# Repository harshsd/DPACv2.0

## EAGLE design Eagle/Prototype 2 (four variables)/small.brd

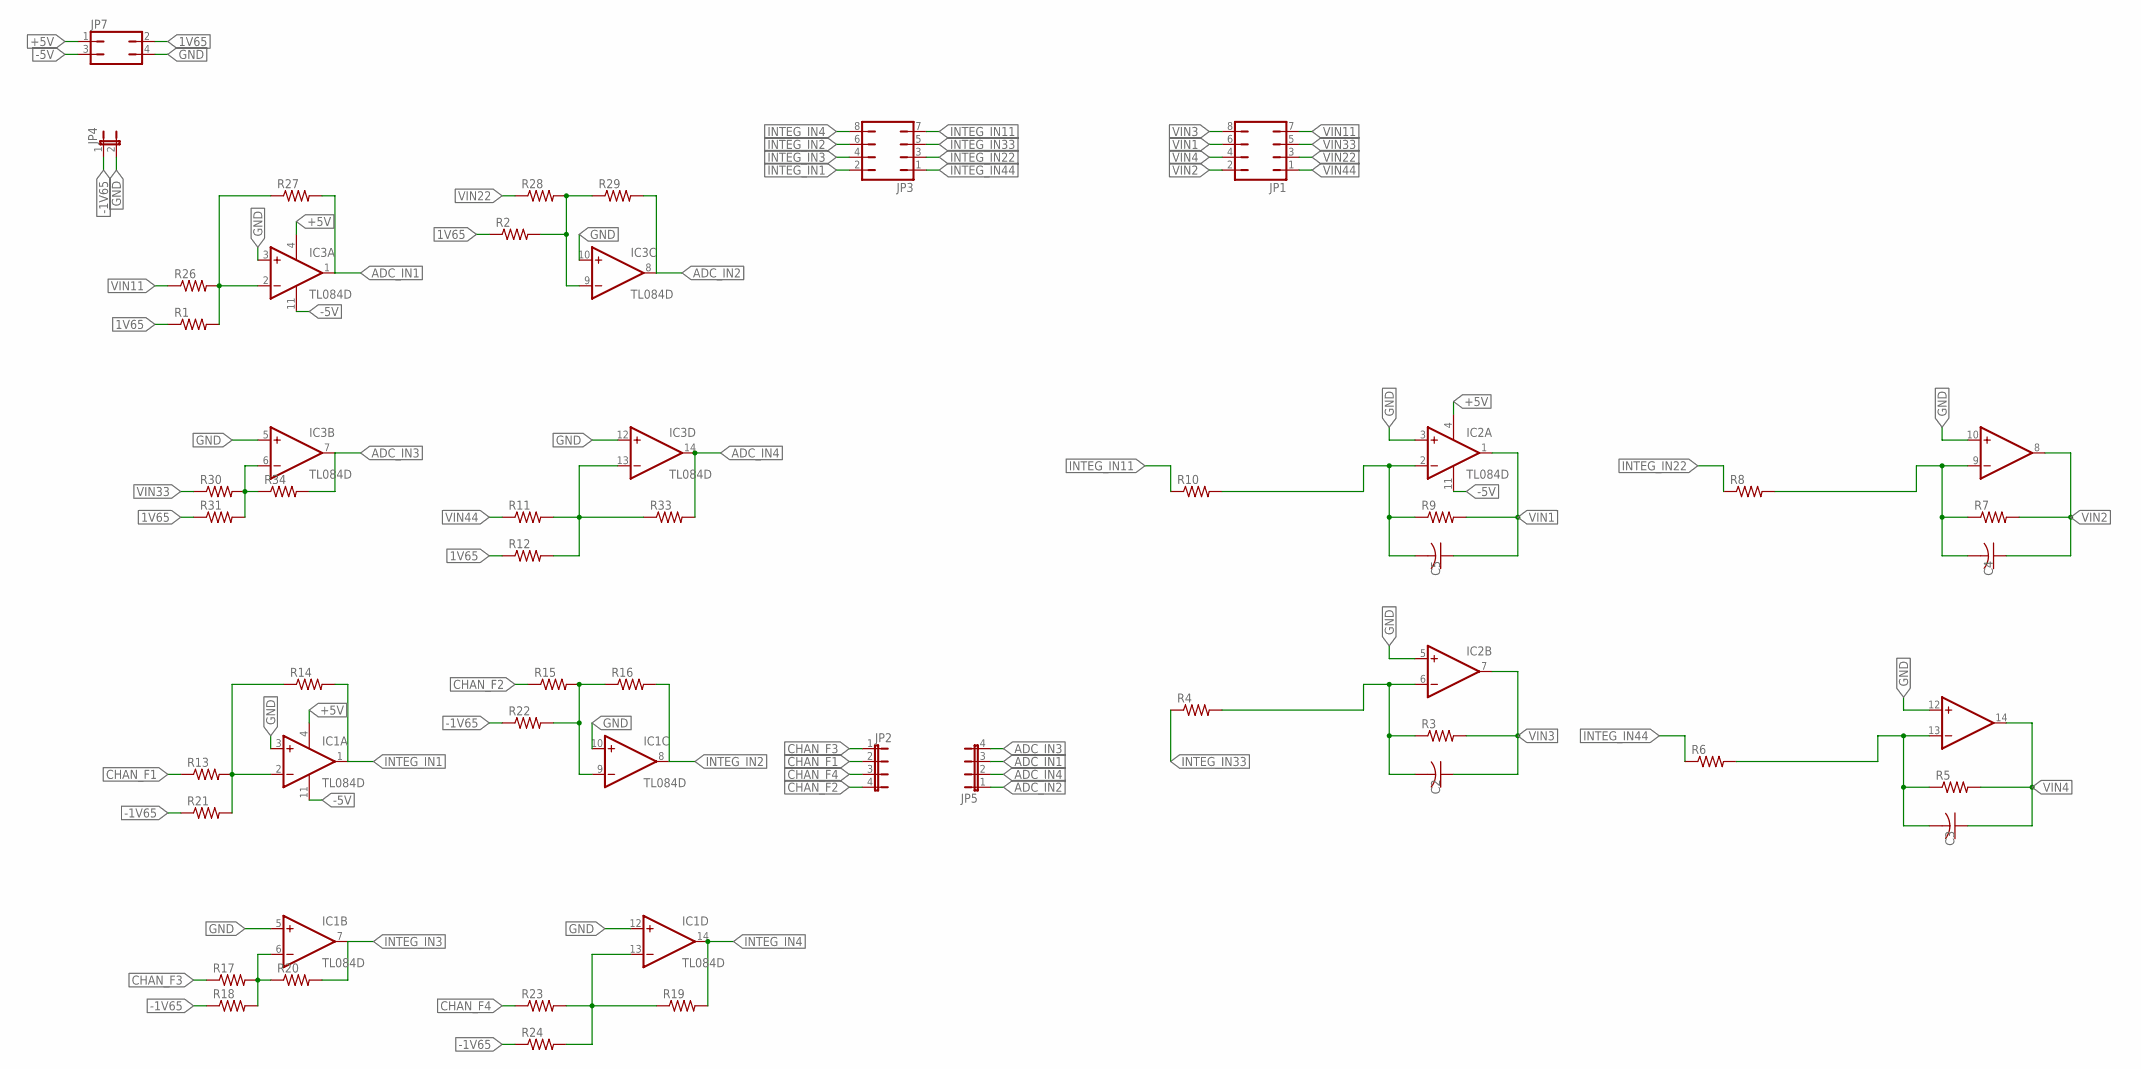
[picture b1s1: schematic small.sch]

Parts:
C2, C3, C4, C5: C-USC1206; C1206
IC1, IC2, IC3: TL084D; SO14
JP1, JP3: JP4Q
JP2, JP5: JP4E; JP4
JP4: JP1E; JP1
JP7: JP2Q
R1, R2, R3, R4, R5, R6, R7, R8, R9, R10, R11, R12, R13, R14, R15, R16, R17, R18, R19, R20, R21, R22, R23, R24, R26, R27, R28, R29, R30, R31, R33, R34: R-US_R1206; R1206

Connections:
1V65: JP7.2, R1.1, R2.1, R12.1, R31.1
+5V: IC1.4 (V+), IC2.4 (V+), IC3.4 (V+), JP7.1
-1V65: JP4.1, R18.1, R21.1, R22.1, R24.1
-5V: IC1.11 (V-), IC2.11 (V-), IC3.11 (V-), JP7.3
ADC_IN1: IC3.1 (OUT), JP5.3, R27.2
ADC_IN2: IC3.8 (OUT), JP5.1, R29.2
ADC_IN3: IC3.7 (OUT), JP5.4, R34.2
ADC_IN4: IC3.14 (OUT), JP5.2, R33.2
CHAN_F1: JP2.2, R13.1
CHAN_F2: JP2.4, R15.1
CHAN_F3: JP2.1, R17.1
CHAN_F4: JP2.3, R23.1
GND: IC1.3 (+IN), IC1.5 (+IN), IC1.10 (+IN), IC1.12 (+IN), IC2.3 (+IN), IC2.5 (+IN), IC2.10 (+IN), IC2.12 (+IN), IC3.3 (+IN), IC3.5 (+IN), IC3.10 (+IN), IC3.12 (+IN), JP4.2, JP7.4
INTEG_IN1: IC1.1 (OUT), JP3.2, R14.2
INTEG_IN2: IC1.8 (OUT), JP3.6, R16.2
INTEG_IN3: IC1.7 (OUT), JP3.4, R20.2
INTEG_IN4: IC1.14 (OUT), JP3.8, R19.2
INTEG_IN11: JP3.7, R10.1
INTEG_IN22: JP3.3, R8.1
INTEG_IN33: JP3.5, R4.1
INTEG_IN44: JP3.1, R6.1
unnamed: IC1.2 (-IN), R13.2, R14.1, R21.2
unnamed: IC1.9 (-IN), R15.2, R16.1, R22.2
unnamed: C5.2, IC2.2 (-IN), R9.1, R10.2
unnamed: C2.2, IC2.6 (-IN), R3.1, R4.2
unnamed: IC1.13 (-IN), R19.1, R23.2, R24.2
unnamed: IC1.6 (-IN), R17.2, R18.2, R20.1
unnamed: C3.2, IC2.13 (-IN), R5.1, R6.2
unnamed: C4.2, IC2.9 (-IN), R7.1, R8.2
unnamed: IC3.2 (-IN), R1.2, R26.2, R27.1
unnamed: IC3.9 (-IN), R2.2, R28.2, R29.1
unnamed: IC3.13 (-IN), R11.2, R12.2, R33.1
unnamed: IC3.6 (-IN), R30.2, R31.2, R34.1
VIN1: C5.1, IC2.1 (OUT), JP1.6, R9.2
VIN2: C4.1, IC2.8 (OUT), JP1.2, R7.2
VIN3: C2.1, IC2.7 (OUT), JP1.8, R3.2
VIN4: C3.1, IC2.14 (OUT), JP1.4, R5.2
VIN11: JP1.7, R26.1
VIN22: JP1.3, R28.1
VIN33: JP1.5, R30.1
VIN44: JP1.1, R11.1

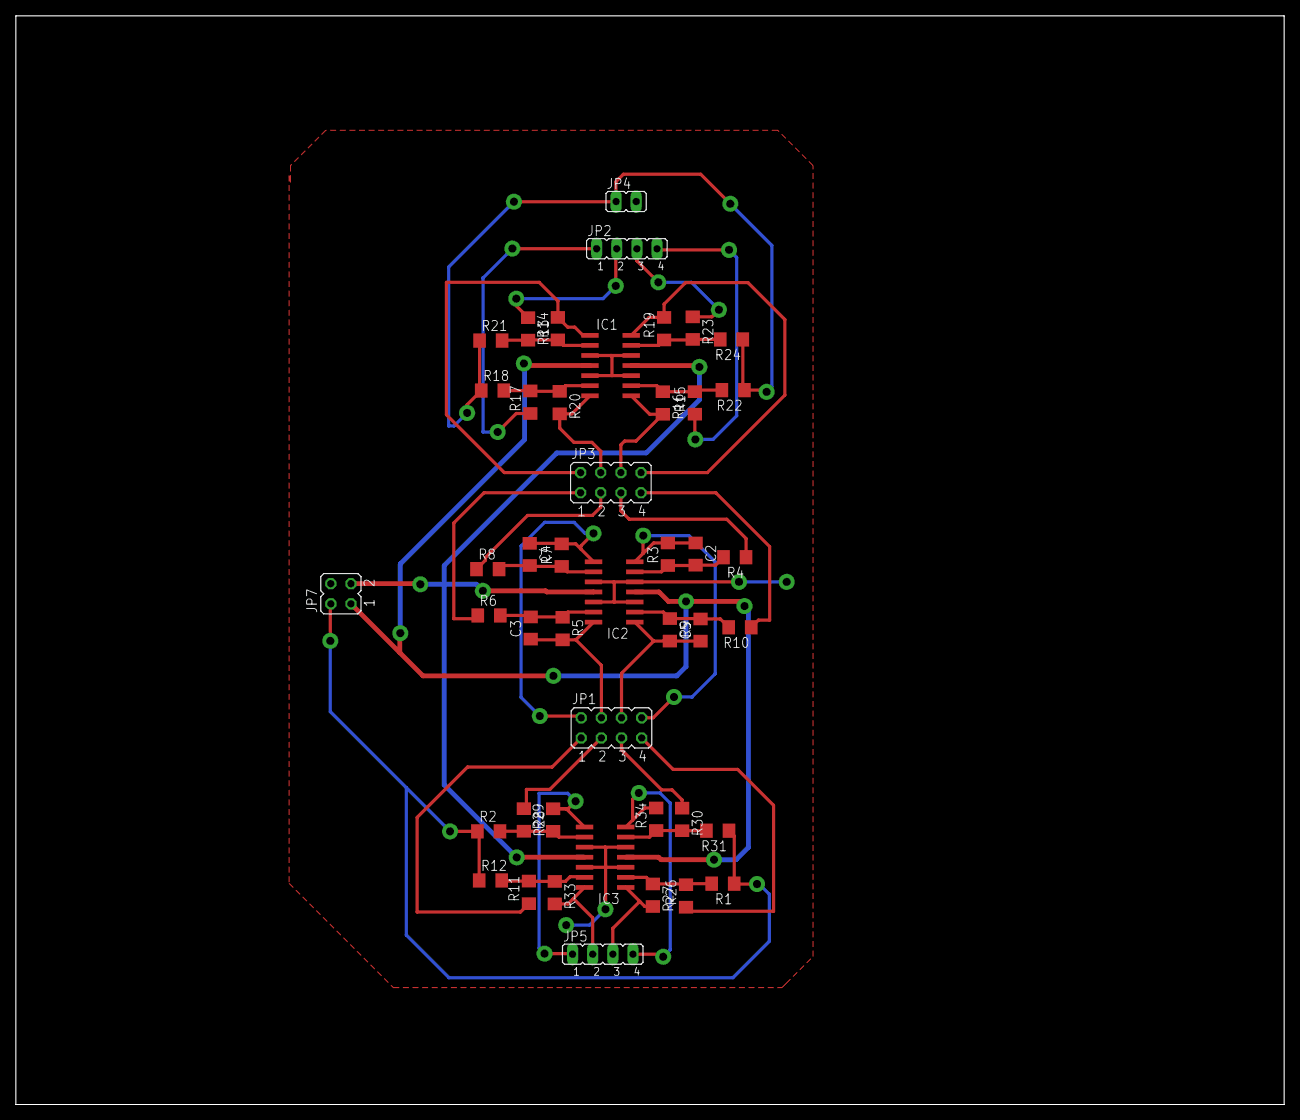
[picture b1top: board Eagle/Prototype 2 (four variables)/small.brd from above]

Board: 2 copper layers, 160.0 x 137.3 mm, 45 parts (0 on the bottom side), 41 nets.

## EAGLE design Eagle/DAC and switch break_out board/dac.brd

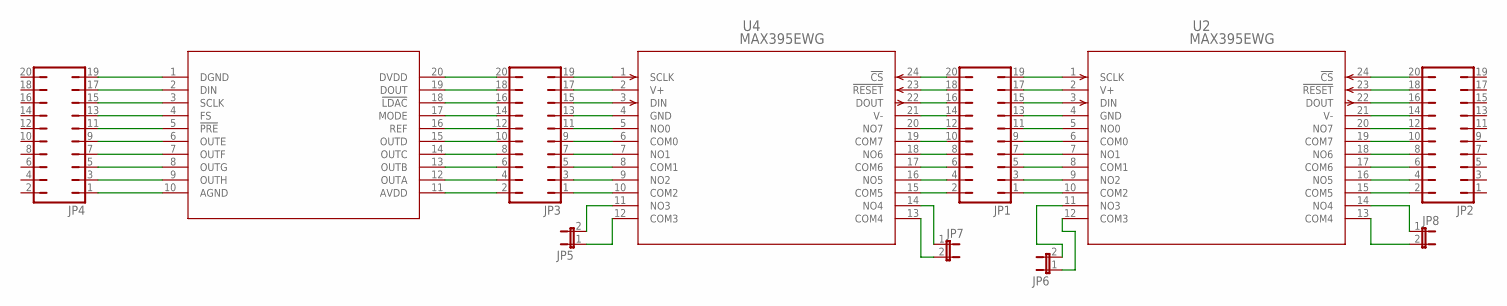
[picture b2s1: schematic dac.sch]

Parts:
JP1, JP2, JP3, JP4: JP10Q
JP5, JP6, JP7, JP8: JP1E; JP1
U1: TLV5610_DW_20; DW20
U2, U4: MAX395EWG; 21-0042B_24

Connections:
unnamed: JP3.19, U4.1 (SCLK)
unnamed: JP3.17, U4.2 (V+)
unnamed: JP3.15, U4.3 (DIN)
unnamed: JP3.13, U4.4 (GND)
unnamed: JP3.11, U4.5 (NO0)
unnamed: JP3.9, U4.6 (COM0)
unnamed: JP3.7, U4.7 (NO1)
unnamed: JP3.5, U4.8 (COM1)
unnamed: JP3.3, U4.9 (NO2)
unnamed: JP3.1, U4.10 (COM2)
unnamed: JP1.20, U4.24 (!CS)
unnamed: JP1.18, U4.23 (!RESET)
unnamed: JP1.16, U4.22 (DOUT)
unnamed: JP1.14, U4.21 (V-)
unnamed: JP1.12, U4.20 (NO7)
unnamed: JP1.10, U4.19 (COM7)
unnamed: JP1.8, U4.18 (NO6)
unnamed: JP1.6, U4.17 (COM6)
unnamed: JP1.4, U4.16 (NO5)
unnamed: JP1.2, U4.15 (COM5)
unnamed: JP3.20, U1.20 (DVDD)
unnamed: JP3.18, U1.19 (DOUT)
unnamed: JP3.16, U1.18 (!LDAC)
unnamed: JP3.14, U1.17 (MODE)
unnamed: JP3.12, U1.16 (REF)
unnamed: JP3.10, U1.15 (OUTD)
unnamed: JP3.8, U1.14 (OUTC)
unnamed: JP3.6, U1.13 (OUTB)
unnamed: JP3.4, U1.12 (OUTA)
unnamed: JP3.2, U1.11 (AVDD)
unnamed: JP4.1, U1.10 (AGND)
unnamed: JP4.3, U1.9 (OUTH)
unnamed: JP4.5, U1.8 (OUTG)
unnamed: JP4.7, U1.7 (OUTF)
unnamed: JP4.9, U1.6 (OUTE)
unnamed: JP4.11, U1.5 (!PRE)
unnamed: JP4.13, U1.4 (FS)
unnamed: JP4.15, U1.3 (SCLK)
unnamed: JP4.17, U1.2 (DIN)
unnamed: JP4.19, U1.1 (DGND)
unnamed: JP1.19, U2.1 (SCLK)
unnamed: JP1.17, U2.2 (V+)
unnamed: JP1.15, U2.3 (DIN)
unnamed: JP1.13, U2.4 (GND)
unnamed: JP1.11, U2.5 (NO0)
unnamed: JP1.9, U2.6 (COM0)
unnamed: JP1.7, U2.7 (NO1)
unnamed: JP1.5, U2.8 (COM1)
unnamed: JP1.3, U2.9 (NO2)
unnamed: JP1.1, U2.10 (COM2)
unnamed: JP2.20, U2.24 (!CS)
unnamed: JP2.18, U2.23 (!RESET)
unnamed: JP2.16, U2.22 (DOUT)
unnamed: JP2.14, U2.21 (V-)
unnamed: JP2.12, U2.20 (NO7)
unnamed: JP2.10, U2.19 (COM7)
unnamed: JP2.8, U2.18 (NO6)
unnamed: JP2.6, U2.17 (COM6)
unnamed: JP2.4, U2.16 (NO5)
unnamed: JP2.2, U2.15 (COM5)
unnamed: JP5.2, U4.11 (NO3)
unnamed: JP5.1, U4.12 (COM3)
unnamed: JP7.1, U4.14 (NO4)
unnamed: JP7.2, U4.13 (COM4)
unnamed: JP6.2, U2.11 (NO3)
unnamed: JP6.1, U2.12 (COM3)
unnamed: JP8.1, U2.14 (NO4)
unnamed: JP8.2, U2.13 (COM4)

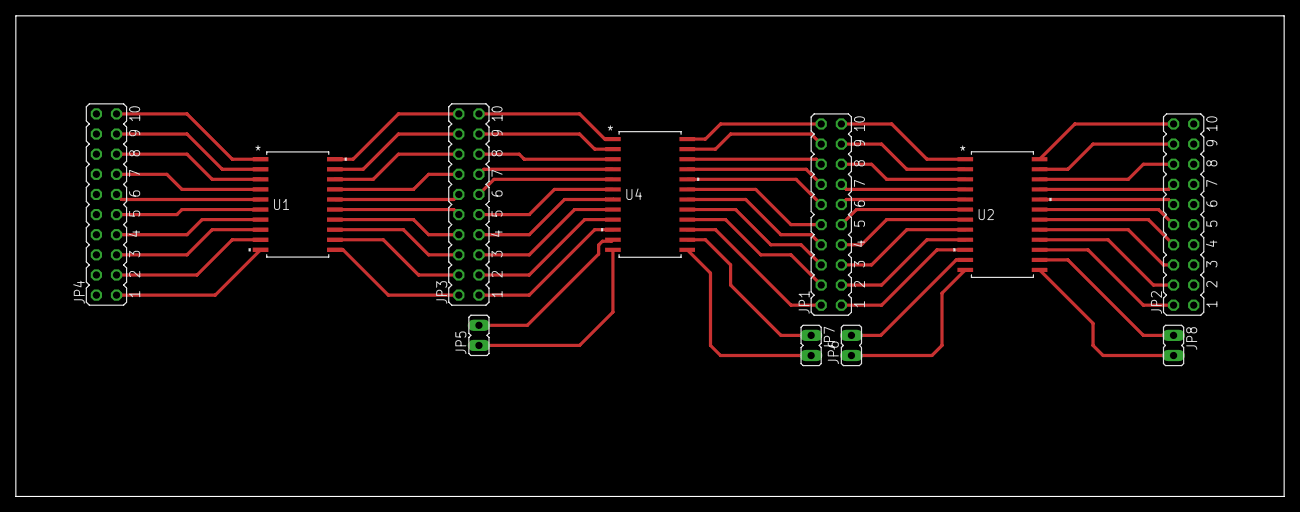
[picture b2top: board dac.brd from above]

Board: 2 copper layers, 160.0 x 60.6 mm, 11 parts (0 on the bottom side), 68 nets.

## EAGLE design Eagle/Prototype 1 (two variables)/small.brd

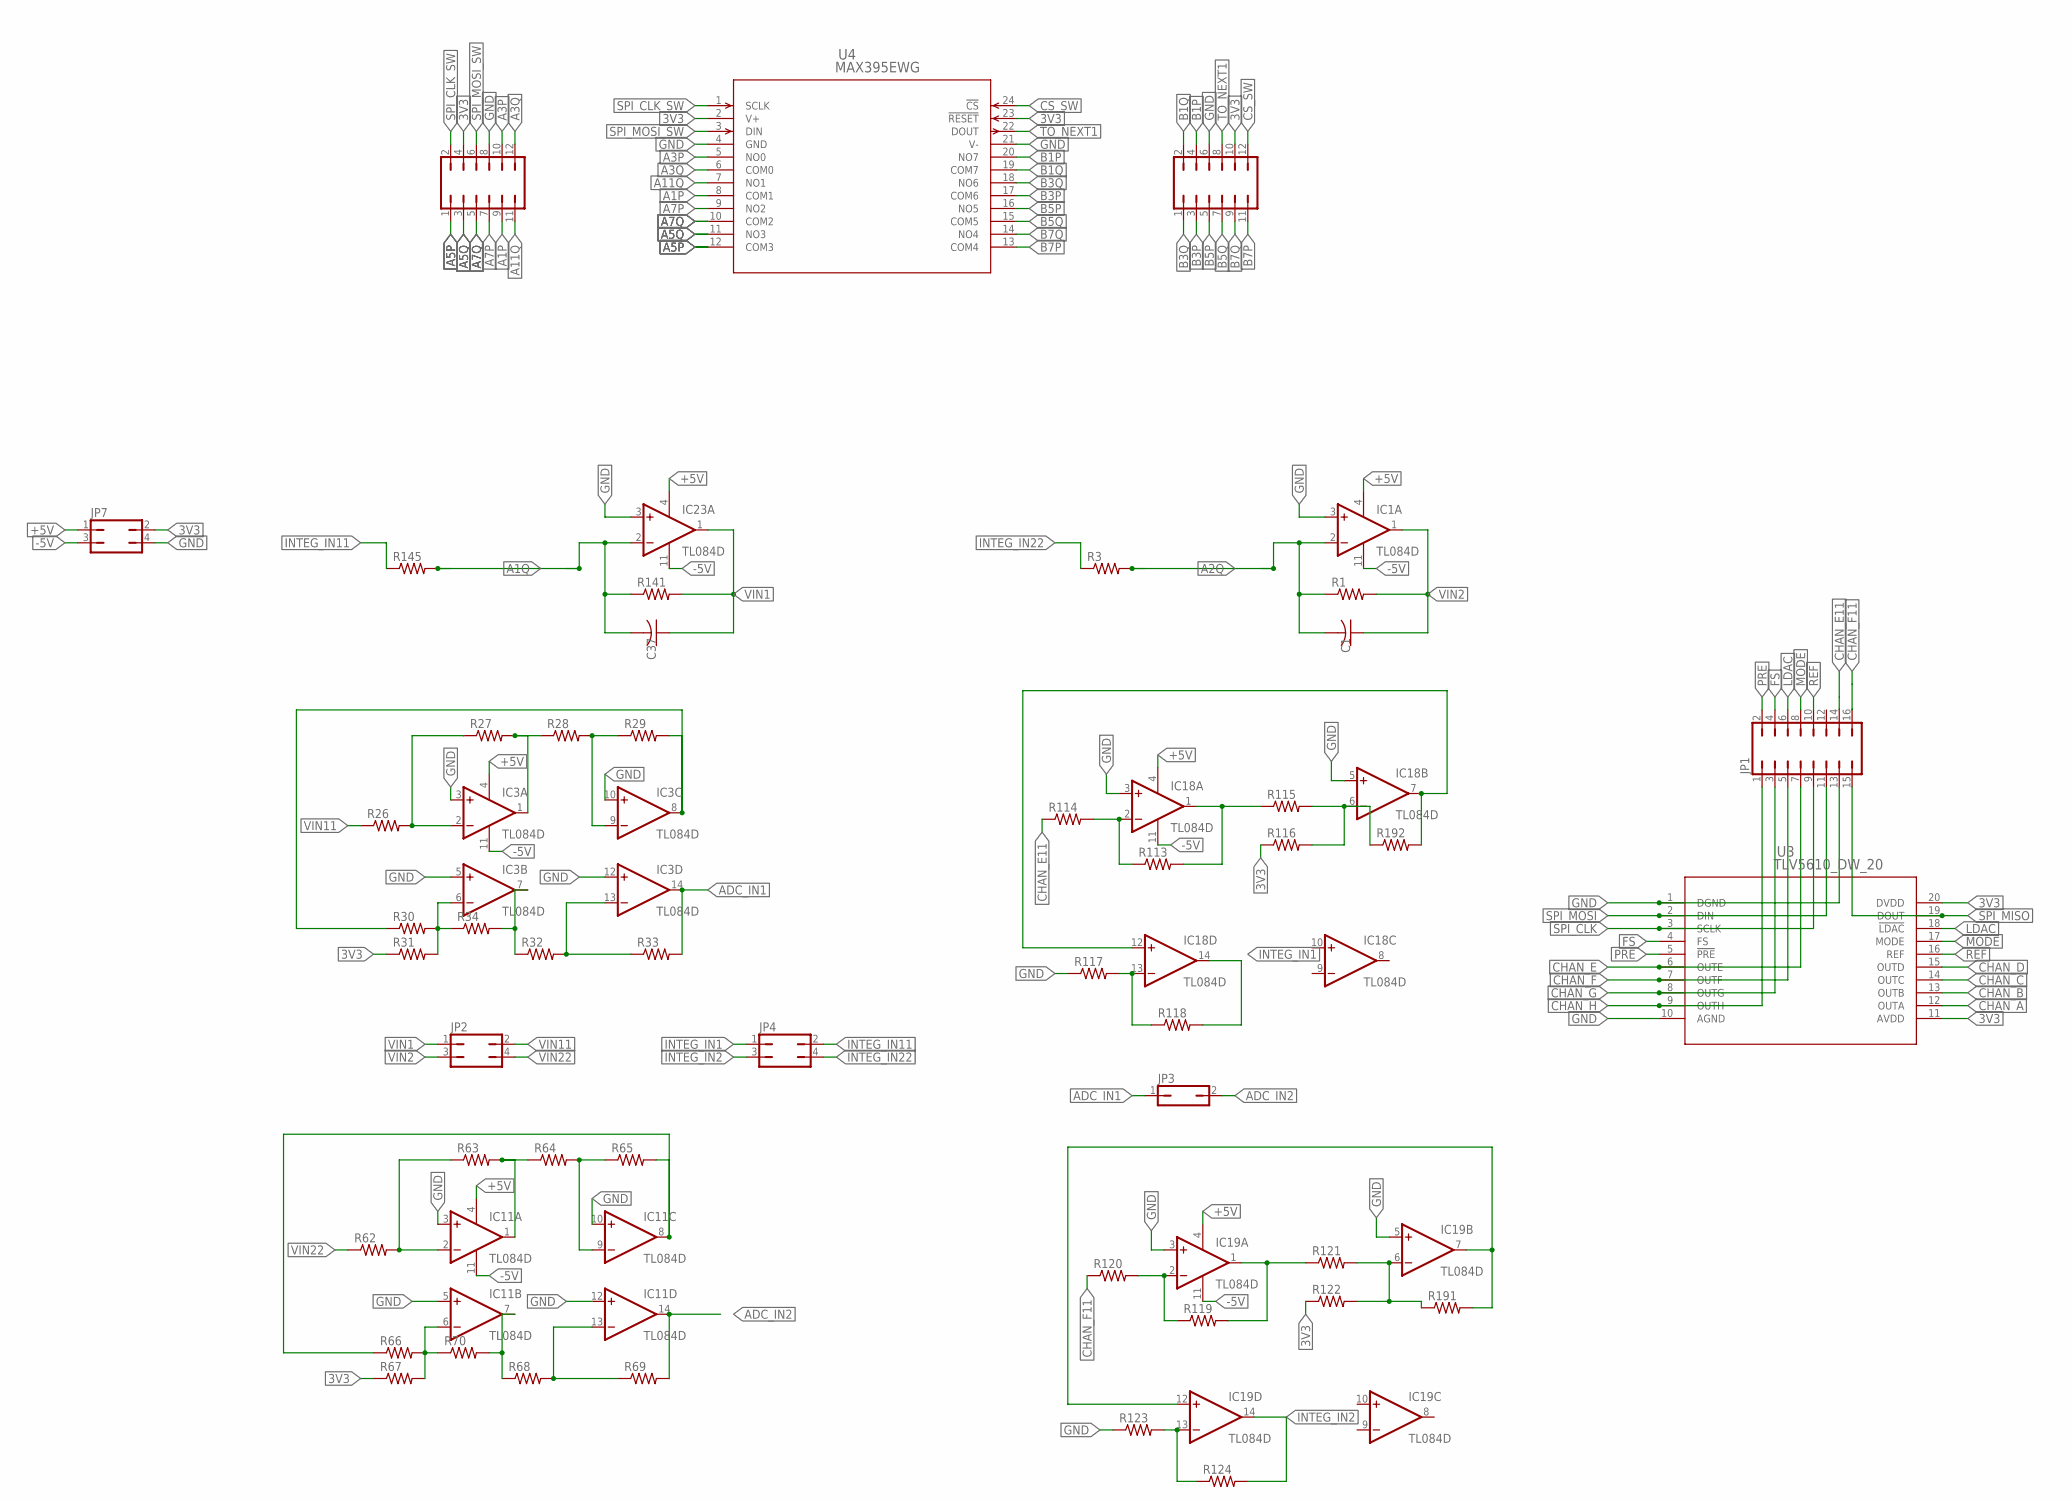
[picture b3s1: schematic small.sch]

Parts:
C1, C37: C-USC1206; C1206
IC1, IC3, IC11, IC18, IC19, IC23: TL084D; SO14
JP1: JP8Q
JP2, JP4, JP7: JP2Q
JP3: JP1Q; JP1
JP5, JP6: JP6Q
R1, R3, R26, R27, R28, R29, R30, R31, R32, R33, R34, R62, R63, R64, R65, R66, R67, R68, R69, R70, R113, R114, R115, R116, R117, R118, R119, R120, R121, R122, R123, R124, R141, R145, R191, R192: R-US_R1206; R1206
U3: TLV5610_DW_20; DW20
U4: MAX395EWG; 21-0042B_24

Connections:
3V3: JP5.4, JP6.10, JP7.2, R31.1, R67.1, R116.1, R122.1, U3.11 (AVDD), U3.20 (DVDD), U4.2 (V+), U4.23 (!RESET)
+5V: IC1.4 (V+), IC3.4 (V+), IC11.4 (V+), IC18.4 (V+), IC19.4 (V+), IC23.4 (V+), JP7.1
-5V: IC1.11 (V-), IC3.11 (V-), IC11.11 (V-), IC18.11 (V-), IC19.11 (V-), IC23.11 (V-), JP7.3
A1P: JP5.9, U4.8 (COM1)
A1Q: C37.2, IC23.2 (-IN), R141.1, R145.2
A2Q: C1.2, IC1.2 (-IN), R1.1, R3.2
A3P: JP5.10, U4.5 (NO0)
A3Q: JP5.12, U4.6 (COM0)
A5P: JP5.1, U4.12 (COM3)
A5Q: JP5.3, U4.11 (NO3)
A7P: JP5.7, U4.9 (NO2)
A7Q: JP5.5, U4.10 (COM2)
A11Q: JP5.11, U4.7 (NO1)
ADC_IN1: IC3.14 (OUT), JP3.1, R33.2
ADC_IN2: IC11.14 (OUT), JP3.2, R69.2
B1P: JP6.4, U4.20 (NO7)
B1Q: JP6.2, U4.19 (COM7)
B3P: JP6.3, U4.17 (COM6)
B3Q: JP6.1, U4.18 (NO6)
B5P: JP6.5, U4.16 (NO5)
B5Q: JP6.7, U4.15 (COM5)
B7P: JP6.11, U4.13 (COM4)
B7Q: JP6.9, U4.14 (NO4)
CHAN_A: U3.12 (OUTA)
CHAN_B: U3.13 (OUTB)
CHAN_C: U3.14 (OUTC)
CHAN_D: U3.15 (OUTD)
CHAN_E: JP1.7, U3.6 (OUTE)
CHAN_E11: JP1.14, R114.1
CHAN_F: JP1.5, U3.7 (OUTF)
CHAN_F11: JP1.16, R120.1
CHAN_G: JP1.3, U3.8 (OUTG)
CHAN_H: JP1.1, U3.9 (OUTH)
CS_SW: JP6.12, U4.24 (!CS)
FS: JP1.4, U3.4 (FS)
GND: IC1.3 (+IN), IC3.3 (+IN), IC3.5 (+IN), IC3.10 (+IN), IC3.12 (+IN), IC11.3 (+IN), IC11.5 (+IN), IC11.10 (+IN), IC11.12 (+IN), IC18.3 (+IN), IC18.5 (+IN), IC19.3 (+IN), IC19.5 (+IN), IC23.3 (+IN), JP1.13, JP5.8, JP6.6, JP7.4, R117.1, R123.1, U3.1 (DGND), U3.10 (AGND), U4.4 (GND), U4.21 (V-)
INTEG_IN1: IC18.14 (OUT), JP4.1, R118.2
INTEG_IN2: IC19.14 (OUT), JP4.3, R124.2
INTEG_IN11: JP4.2, R145.1
INTEG_IN22: JP4.4, R3.1
LDAC: JP1.6, U3.18 (!LDAC)
MODE: JP1.8, U3.17 (MODE)
unnamed: IC3.2 (-IN), R26.2, R27.1
unnamed: IC3.1 (OUT), R27.2, R28.1
unnamed: IC3.9 (-IN), R28.2, R29.1
unnamed: IC3.8 (OUT), R29.2, R30.1
unnamed: IC3.7 (OUT), R32.1, R34.2
unnamed: IC3.13 (-IN), R32.2, R33.1
unnamed: IC3.6 (-IN), R30.2, R31.2, R34.1
unnamed: IC11.2 (-IN), R62.2, R63.1
unnamed: IC11.1 (OUT), R63.2, R64.1
unnamed: IC11.9 (-IN), R64.2, R65.1
unnamed: IC11.8 (OUT), R65.2, R66.1
unnamed: IC11.7 (OUT), R68.1, R70.2
unnamed: IC11.13 (-IN), R68.2, R69.1
unnamed: IC11.6 (-IN), R66.2, R67.2, R70.1
unnamed: IC18.2 (-IN), R113.1, R114.2
unnamed: IC18.1 (OUT), R113.2, R115.1
unnamed: IC18.6 (-IN), R115.2, R116.2, R192.1
unnamed: IC18.13 (-IN), R117.2, R118.1
unnamed: IC18.7 (OUT), IC18.12 (+IN), R192.2
unnamed: IC19.2 (-IN), R119.1, R120.2
unnamed: IC19.1 (OUT), R119.2, R121.1
unnamed: IC19.6 (-IN), R121.2, R122.2, R191.1
unnamed: IC19.13 (-IN), R123.2, R124.1
unnamed: IC19.7 (OUT), IC19.12 (+IN), R191.2
PRE: JP1.2, U3.5 (!PRE)
REF: JP1.10, U3.16 (REF)
SPI_CLK: JP1.9, U3.3 (SCLK)
SPI_CLK_SW: JP5.2, U4.1 (SCLK)
SPI_MISO: JP1.15, U3.19 (DOUT)
SPI_MOSI: JP1.11, U3.2 (DIN)
SPI_MOSI_SW: JP5.6, U4.3 (DIN)
TO_NEXT1: JP6.8, U4.22 (DOUT)
VIN1: C37.1, IC23.1 (OUT), JP2.1, R141.2
VIN2: C1.1, IC1.1 (OUT), JP2.3, R1.2
VIN11: JP2.2, R26.1
VIN22: JP2.4, R62.1

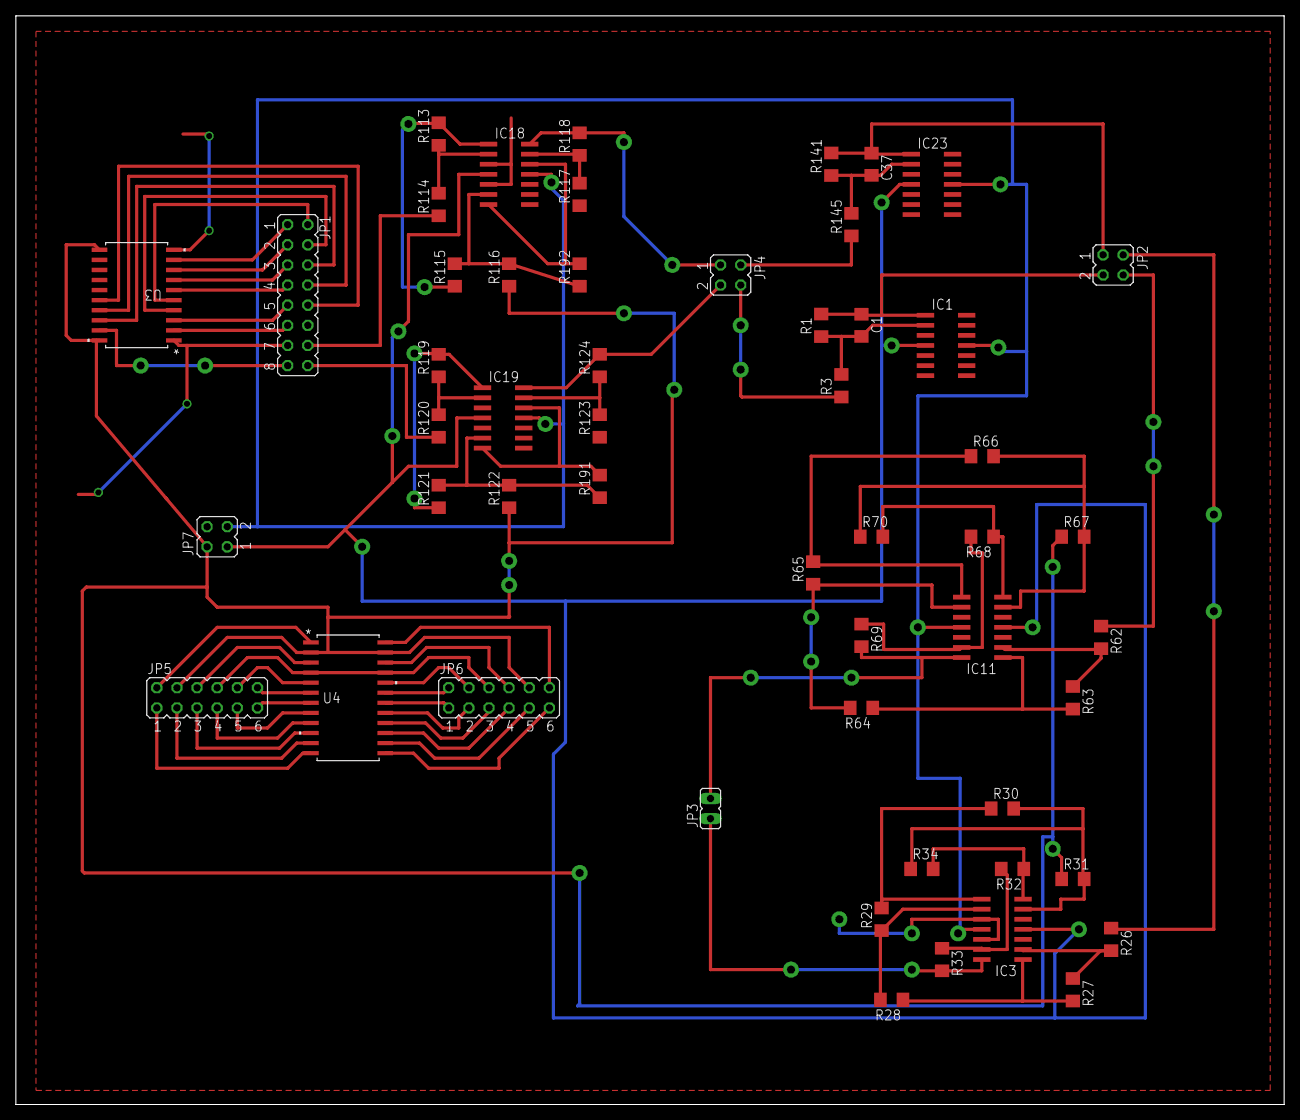
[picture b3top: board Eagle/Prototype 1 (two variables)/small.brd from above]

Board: 2 copper layers, 160.0 x 137.3 mm, 53 parts (0 on the bottom side), 74 nets.

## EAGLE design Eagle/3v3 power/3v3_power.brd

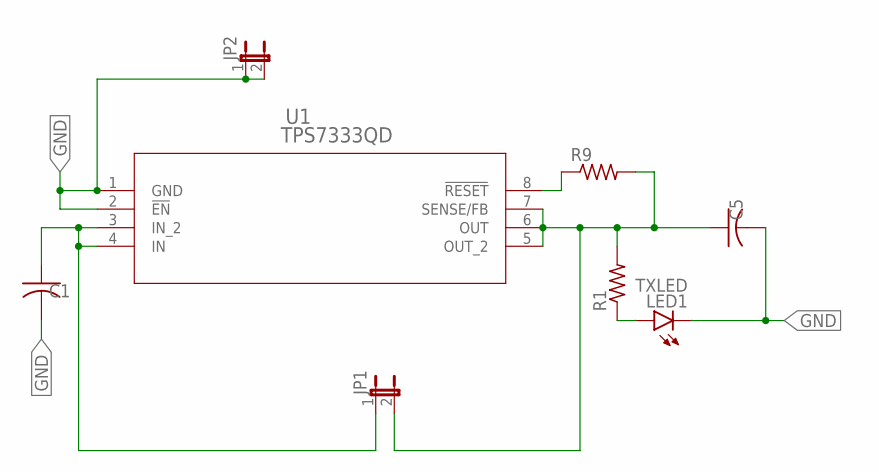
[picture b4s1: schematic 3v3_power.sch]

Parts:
C1, C5: C-USC1206; C1206
JP1, JP2: JP1E; JP1
LED1: TXLED; CHIPLED_1206
R1, R9: R-US_R1206; R1206
U1: TPS7333QD; D8

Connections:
GND: C1.2, C5.2, JP2.1, JP2.2, LED1.C, U1.1 (GND), U1.2 (!EN)
unnamed: C1.1, JP1.1, U1.3 (IN_2), U1.4 (IN)
unnamed: C5.1, JP1.2, R1.2, R9.2, U1.5 (OUT_2), U1.6 (OUT), U1.7 (SENSE/FB)
unnamed: R9.1, U1.8 (!RESET)
unnamed: LED1.A, R1.1

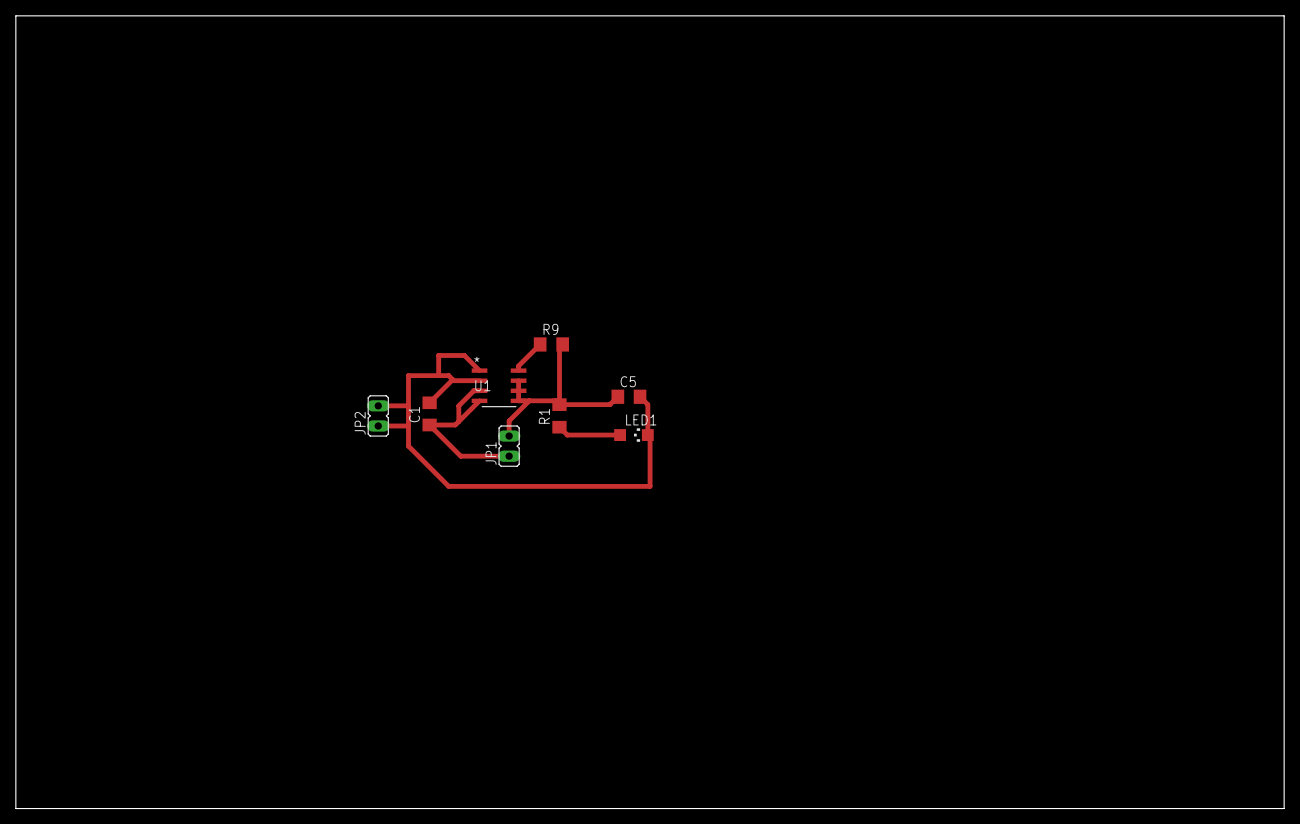
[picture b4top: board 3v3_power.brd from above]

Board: 2 copper layers, 160.0 x 100.0 mm, 8 parts (0 on the bottom side), 5 nets.

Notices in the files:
parts and their libraries:
SparkFun-Capacitors: Licensing: Creative Commons ShareAlike 4.0 International - https://creativecommons.org/licenses/by-sa/4.0
